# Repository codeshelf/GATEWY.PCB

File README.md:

# GATEWY.PCB
The KW2 gateway radio board

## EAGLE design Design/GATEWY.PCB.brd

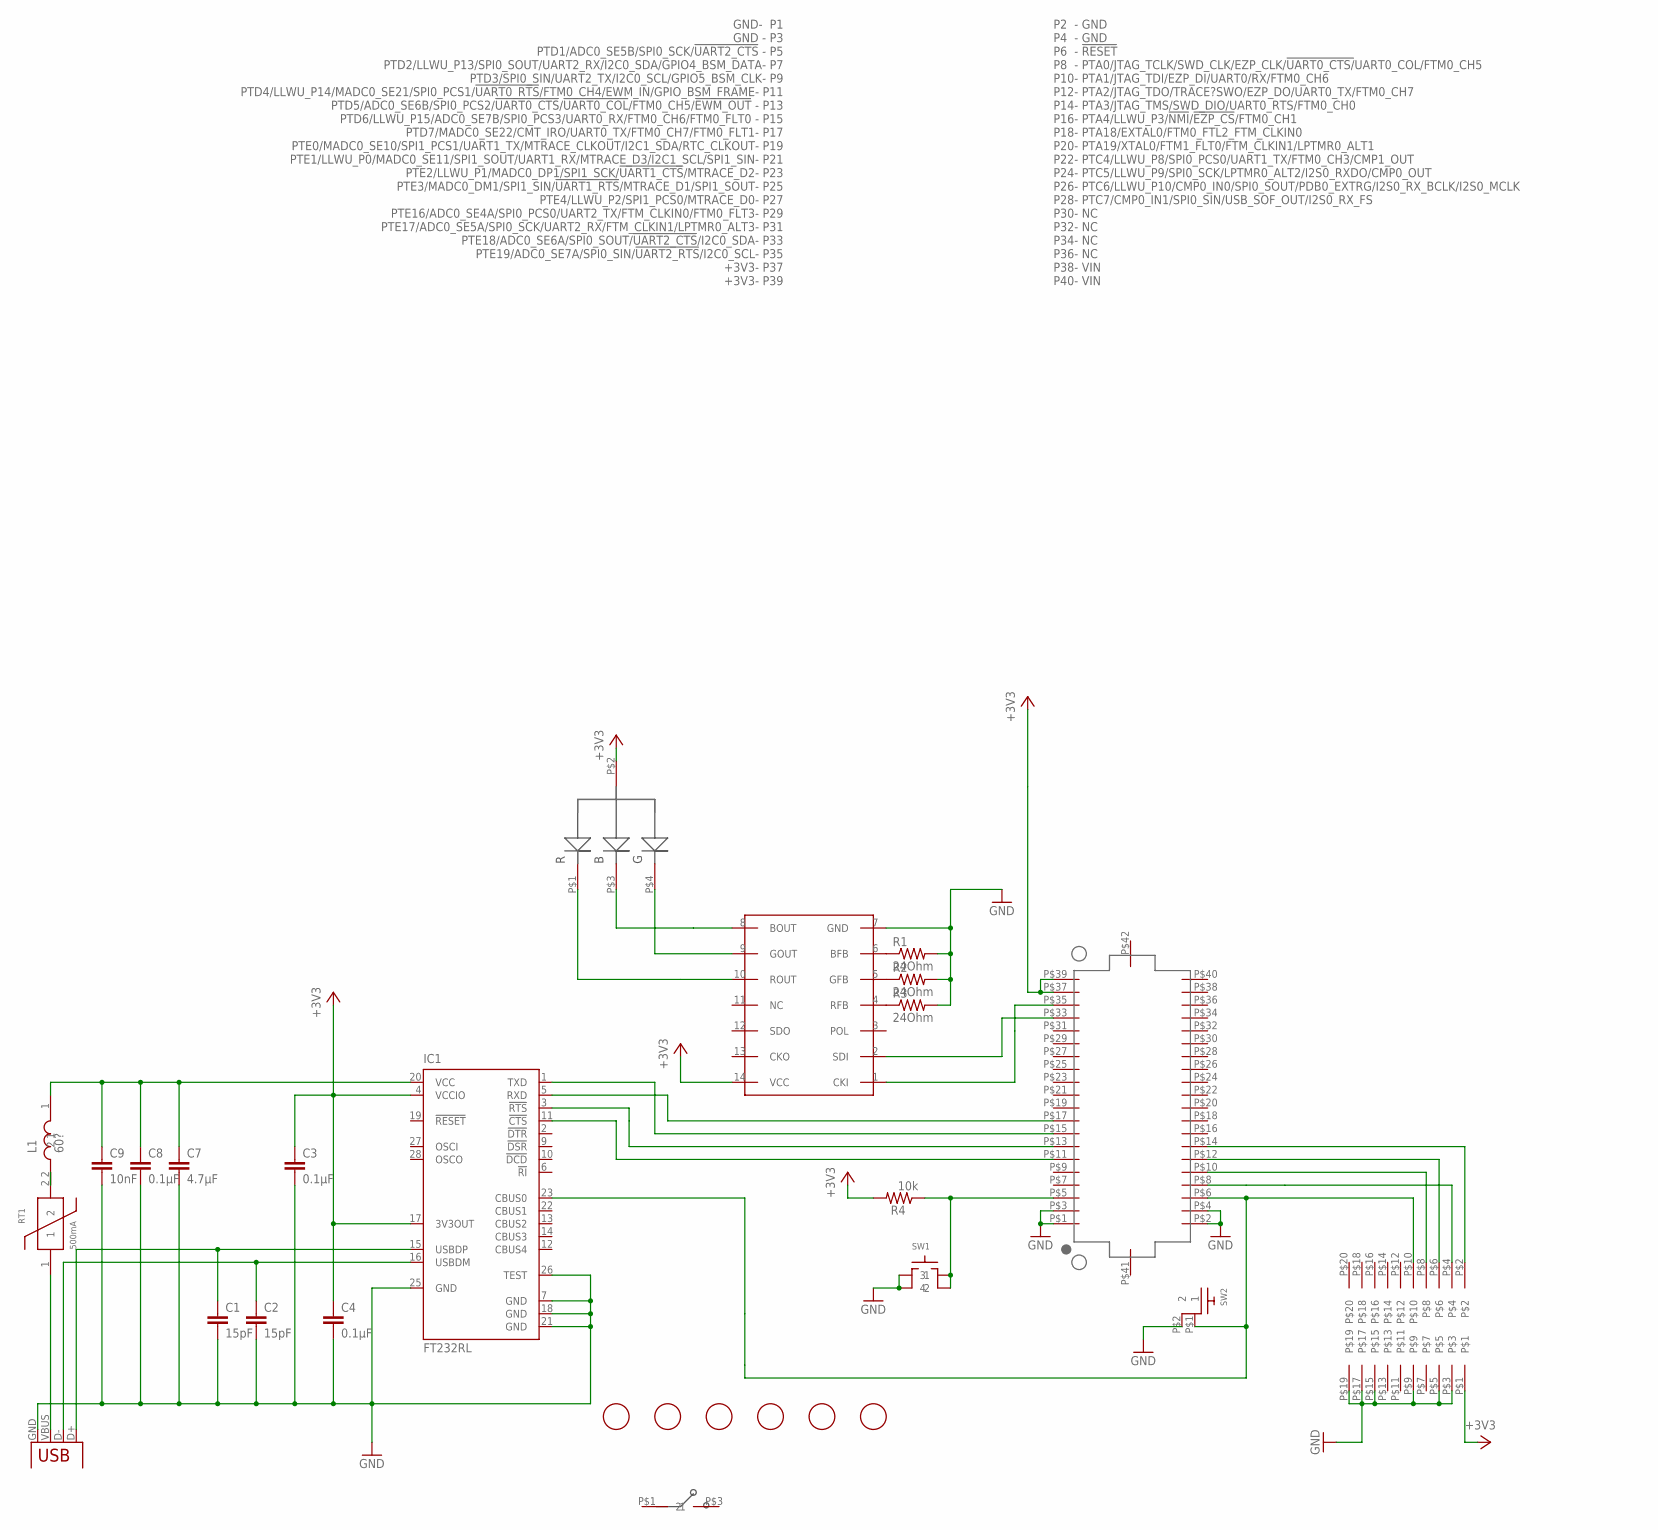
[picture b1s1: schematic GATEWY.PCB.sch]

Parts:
AWESOME: CJS
C1, C2: 15pF; RF-C0402
C3, C4, C8: 0.1µF; RF-C0402
C7: 4.7µF; RF-C0805
C9: 10nF; RF-C0402
IC1: FT232RL; SSOP28
JTAG: 2X10JTAGSMD; 2X10JTAG-SMD
KW2: DF12_F
L1: 60?; RF-L0603
LED1: RGLBED; RGBLED
R1, R2, R3: 24Ohm; RF-C0805
R4: 10k; RF-C0805
RT1: 500mA; C1210
SW1: SWITCH-TACTILE; ESWITCH-TL3301PF
SW2: RA_BUTTON
U1: WS2801; SO14
U$14, U$18, U$25, U$26, U$27, U$28: FIDUCIAL; FIDUCIAL_1MM
X1: USBPTH; USB-B-PTH

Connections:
+3V3: C3.1, C4.1, IC1.4 (VCCIO), IC1.17 (3V3OUT), JTAG.P$1, KW2.P$37 (+3V3), KW2.P$39 (+3V3), LED1.P$2 (ANODE), R4.2, U1.14 (VCC)
CTS: IC1.3 (!RTS), KW2.P$13 (PTD5/ADC0_SE6B/SPI0_PCS2/!UART0_CTS!/!U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)
GND: C1.2, C2.2, C3.2, C4.2, C7.2, C8.2, C9.2, IC1.7 (GND), IC1.18 (GND), IC1.21 (GND), IC1.25 (GND), IC1.26 (TEST), JTAG.P$3, JTAG.P$5, JTAG.P$9, JTAG.P$15, JTAG.P$17, JTAG.P$19, KW2.P$1 (GND), KW2.P$2 (GND), KW2.P$3 (GND), KW2.P$4 (GND), R1.2, R2.2, R3.2, SW1.1, SW1.2, SW2.P$2 (2), U1.7 (GND), X1.GND
JTAG_CLK: JTAG.P$4, KW2.P$8 (PTA0/JTAG_TCLK/SWD_CLK/EZP_CLK/!UART0_C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)
JTAG_TDI: JTAG.P$8, KW2.P$10 (PTA1/JTAG_TDI/EZP_DI/UART0/RX/FTM0_CH6)
JTAG_TDO: JTAG.P$6, KW2.P$12 (PTA2/JTAG_TDO/TRACE?SWO/EZP_DO/UART0_TX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)
JTAG_TMS: JTAG.P$2, KW2.P$14 (PTA3/JTAG_TMS/SWD_DIO/UART0_RTS/FTM0_CH0)
unnamed: LED1.P$4 (GREEN), U1.9 (GOUT)
unnamed: LED1.P$3 (BLUE), U1.8 (BOUT)
unnamed: LED1.P$1 (RED), U1.10 (ROUT)
unnamed: KW2.P$33 (PTE18/ADC0_SE6A/SPI0_SOUT/!UART2_CTS!/I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), U1.2 (SDI)
unnamed: R1.1, U1.6 (BFB)
unnamed: R2.1, U1.5 (GFB)
unnamed: R3.1, U1.4 (RFB)
unnamed: KW2.P$35 (PTE19/ADC0_SE7A/SPI0_SIN/!UART2_RTS!/I2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), U1.1 (CKI)
unnamed: KW2.P$5 (PTD1/ADC0_SE5B/SPI0_SCK/!UART2_CTS), R4.1, SW1.3, SW1.4
RESET: IC1.23 (CBUS0), JTAG.P$10, KW2.P$6 (!RESET), SW2.P$1 (1)
RTS: IC1.11 (!CTS), KW2.P$11 (PTD4/LLWU_P14/MADC0_SE21/SPI0_PCS1/!UAR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)
RX: IC1.1 (TXD), KW2.P$15 (PTD6/LLWU_P15/ADC0_SE7B/SPI0_PCS3/UART0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)
TX: IC1.5 (RXD), KW2.P$17 (PTD7/MADC0_SE22/CMT_IRO/UART0_TX/FTM0_C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)
USB+: C1.1, IC1.15 (USBDP), X1.D+
USB-: C2.1, IC1.16 (USBDM), X1.D-
USB_VCC_1: RT1.1, X1.VBUS
USB_VCC_2: L1.2, RT1.2
USB_VCC_3: C7.1, C8.1, C9.1, IC1.20 (VCC), L1.1

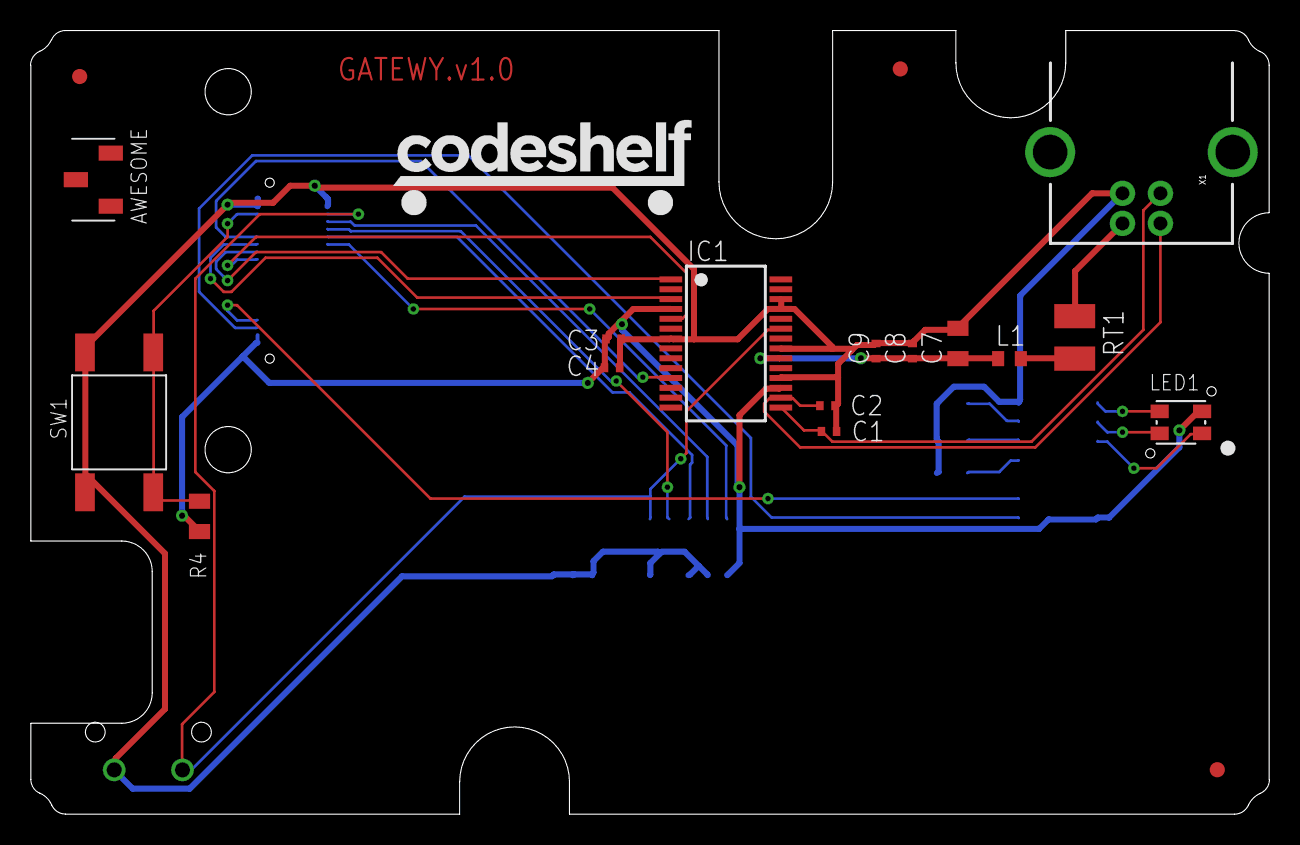
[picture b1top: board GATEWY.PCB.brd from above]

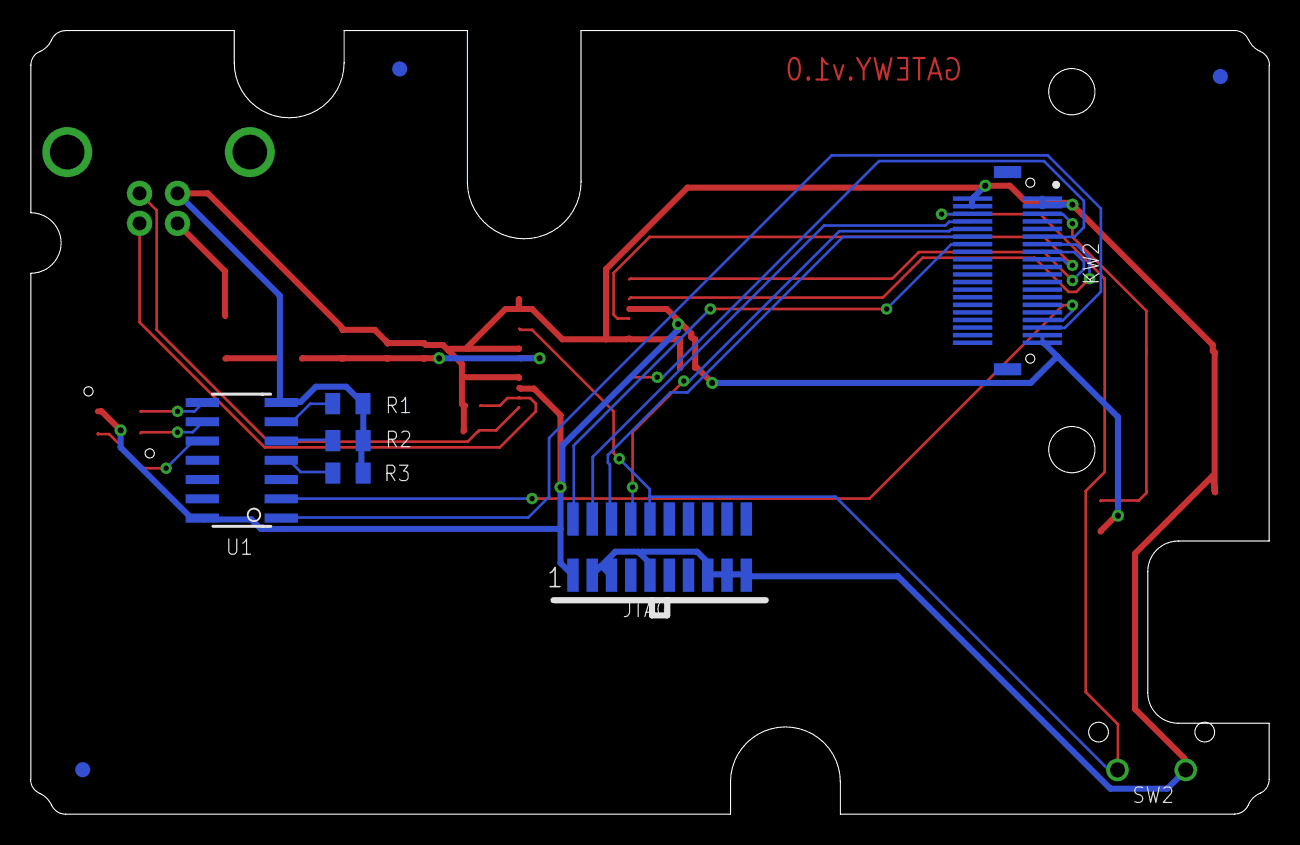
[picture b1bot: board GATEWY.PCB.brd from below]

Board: 2 copper layers, 81.7 x 51.7 mm, 28 parts (10 on the bottom side), 25 nets.

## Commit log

2016-01-18 First test design
    This is the first design for the shop to build/test.
2016-01-19 Use the new Codeshelf DRU file to generate and test the board.
2016-01-19 Update CAM and LMD files for milling
2016-01-20 Update CAM and LMD Files - fix text
2016-01-28 Change the JTAG header to SMT
    Also remove the SWD header.
2016-02-24 Redo the board with larger vias (from the new CS "std" DRU file.
2016-02-26 Fix a problem with 3.3V
2016-02-27 Fix the FTDI UART pins.
2016-02-29 first round cam files
2016-03-18 Add centroids.
2016-03-24 Fix the design so it generates a correct BOM
2016-03-27 Remove bougs layers and add an fab note.
